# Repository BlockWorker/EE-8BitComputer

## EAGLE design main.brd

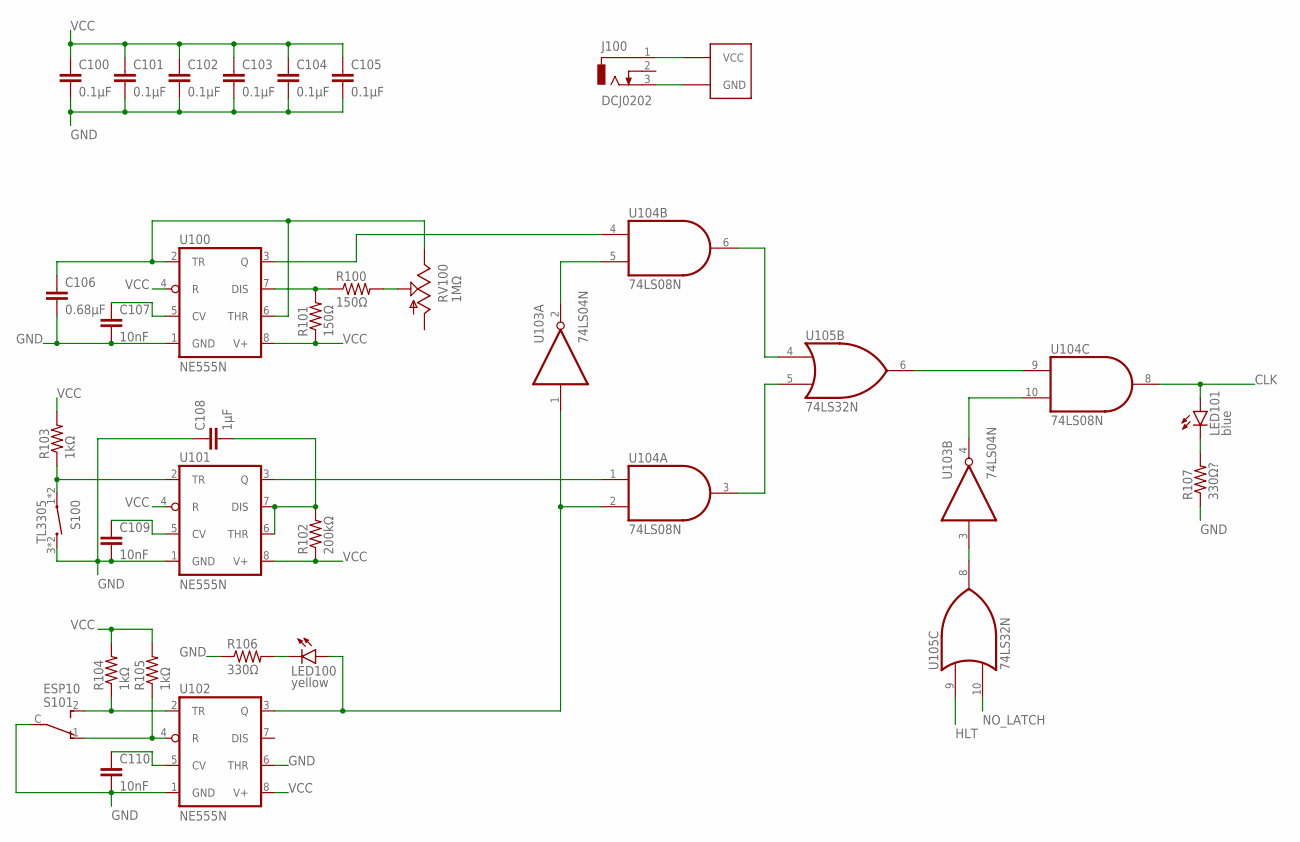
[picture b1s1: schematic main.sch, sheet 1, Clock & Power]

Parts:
C100, C101, C102, C103, C104, C105: 0.1µF; C0805K
C106: 0.68µF; C0805K
C107, C109, C110: 10nF; C0805K
C108: 1µF; C0805K
J100: DCJ0202
LED100: yellow; LED3MM
LED101: blue; LED3MM
R100, R101: 150Ω; R0805
R102: 200kΩ; R0805
R103, R104, R105: 1kΩ; R0805
R106: 330Ω; R0805
R107: 330Ω?; R0805
RV100: 1MΩ; CA9V
S100: TL3305; TL3305_MICROSWITCH
S101: ESP10
U100, U101, U102: NE555N; DIL08
U103: 74LS04N; DIL14
U104: 74LS08N; DIL14
U105: 74LS32N; DIL14

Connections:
!CLK_ENABLE: U103.3 (I), U105.8 (O)
!CLK_SWITCH: U103.2 (O), U104.5 (I1)
CLK: LED101.A, U104.8 (O); also elsewhere on the board
CLK_AUTO: U104.6 (O), U105.4 (I0)
CLK_AUTO_RAW: U100.3 (Q), U104.4 (I0)
CLK_ENABLE: U103.4 (O), U104.10 (I1)
CLK_MANUAL: U104.3 (O), U105.5 (I1)
CLK_MANUAL_RAW: U101.3 (Q), U104.1 (I0)
CLK_RAW: U104.9 (I0), U105.6 (O)
CLK_SWITCH: LED100.A, U102.3 (Q), U103.1 (I), U104.2 (I1)
GND: C100.2, C101.2, C102.2, C103.2, C104.2, C105.2, C106.2, C107.2, C108.1, C109.2, C110.2, J100.3, R106.1, R107.1, S100.3 (2), S100.4 (2), S101.C, U100.1 (GND), U101.1 (GND), U102.1 (GND), U102.6 (THR), U103.7 (GND), U104.7 (GND), U105.7 (GND); also elsewhere on the board
HLT: U105.9 (I0); also elsewhere on the board
LED100_GND: LED100.K (C), R106.2
LED101_GND: LED101.K (C), R107.2
NO_LATCH: U105.10 (I1); also elsewhere on the board
U100_CAP: C106.1, RV100.E, U100.2 (TR), U100.6 (THR)
U100_CV: C107.1, U100.5 (CV)
U100_DIS: R100.1, R101.2, U100.7 (DIS)
U100_DIS_INT: R100.2, RV100.S
U101_CAP: C108.2, R102.2, U101.6 (THR), U101.7 (DIS)
U101_CV: C109.1, U101.5 (CV)
U101_TR: R103.1, S100.1, S100.2 (1), U101.2 (TR)
U102_CV: C110.1, U102.5 (CV)
U102_R: R105.1, S101.1 (O), U102.4 (R)
U102_TR: R104.1, S101.2 (S), U102.2 (TR)
VCC: C100.1, C101.1, C102.1, C103.1, C104.1, C105.1, J100.1, R101.1, R102.1, R103.2, R104.2, R105.2, U100.4 (R), U100.8 (V+), U101.4 (R), U101.8 (V+), U102.8 (V+), U103.14 (VCC), U104.14 (VCC), U105.14 (VCC); also elsewhere on the board

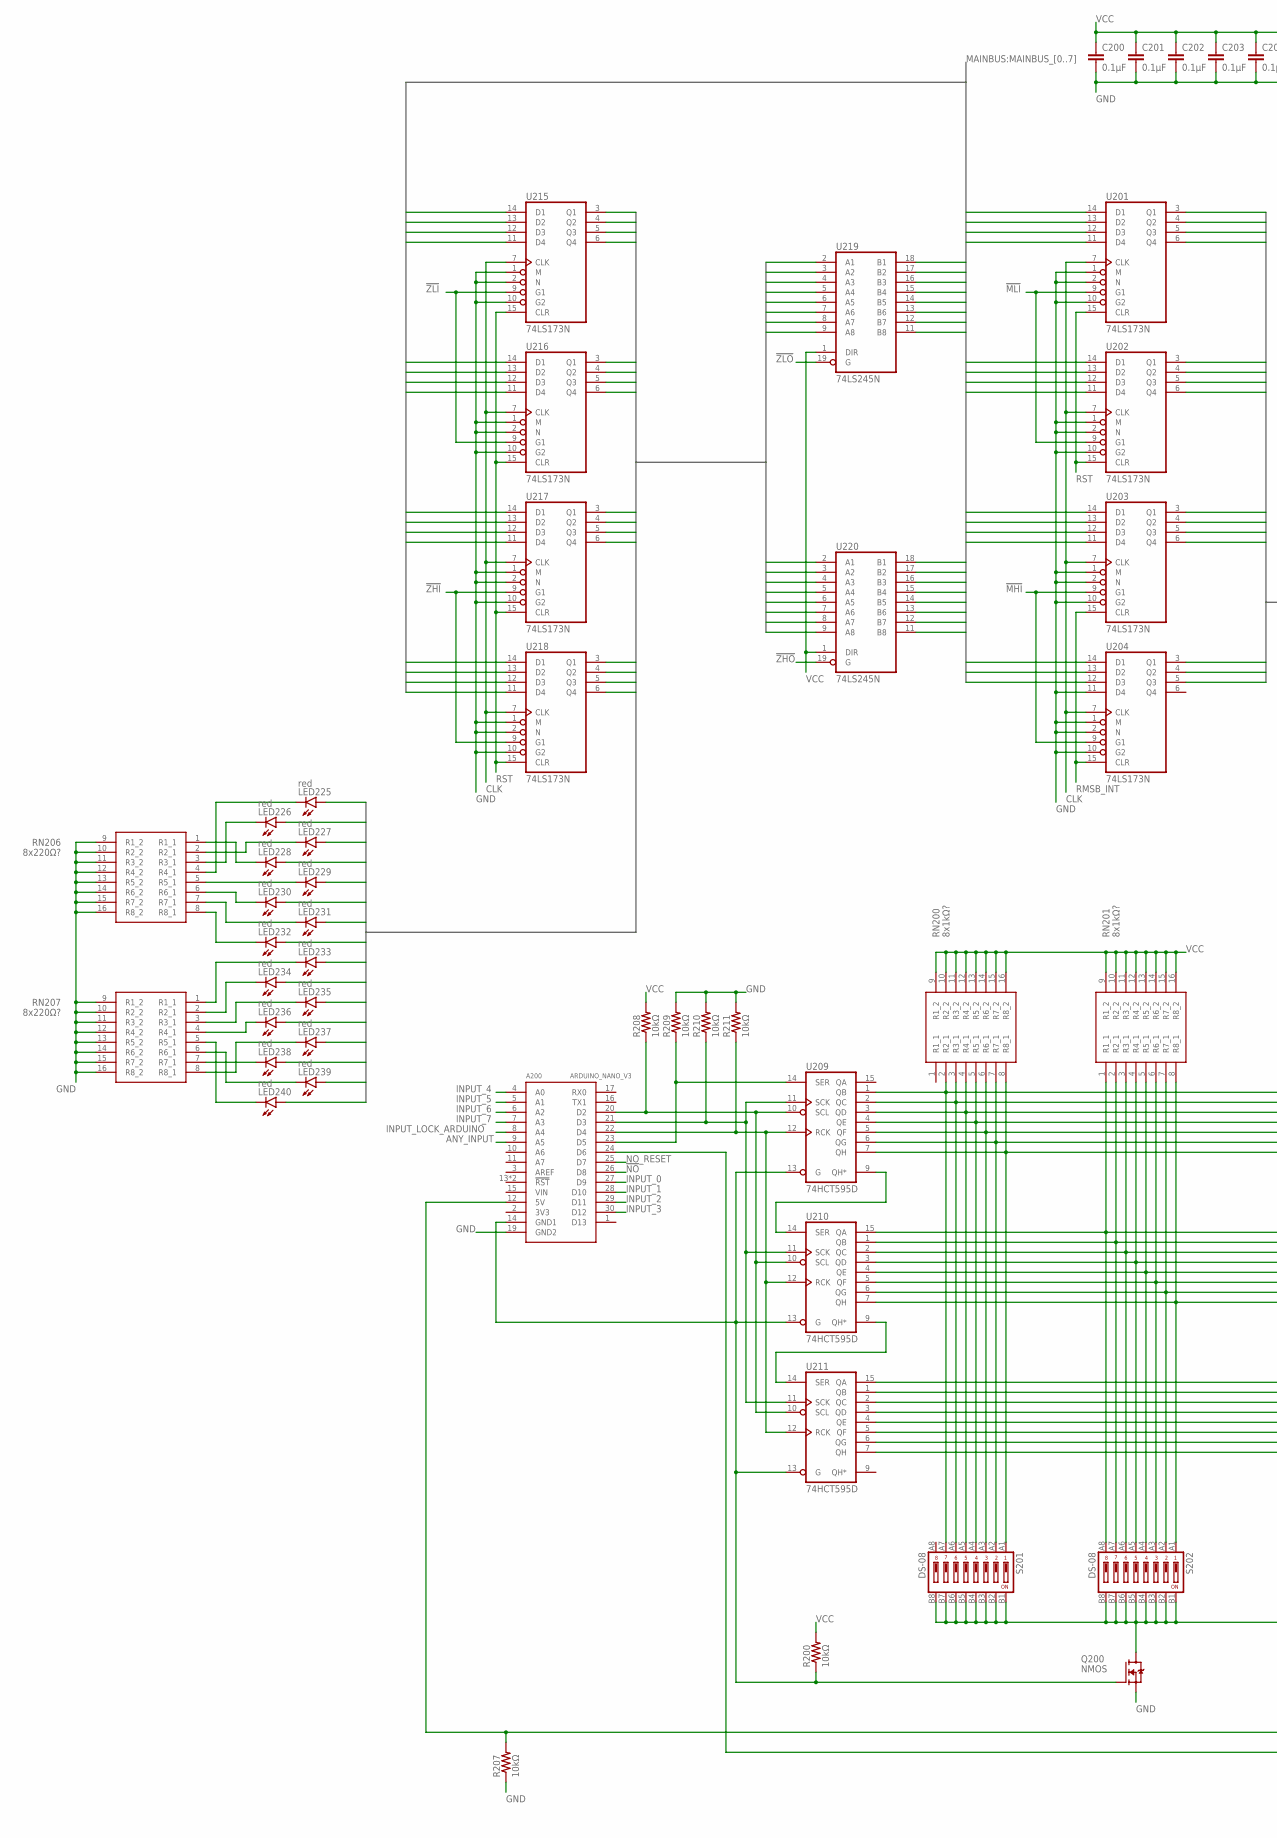
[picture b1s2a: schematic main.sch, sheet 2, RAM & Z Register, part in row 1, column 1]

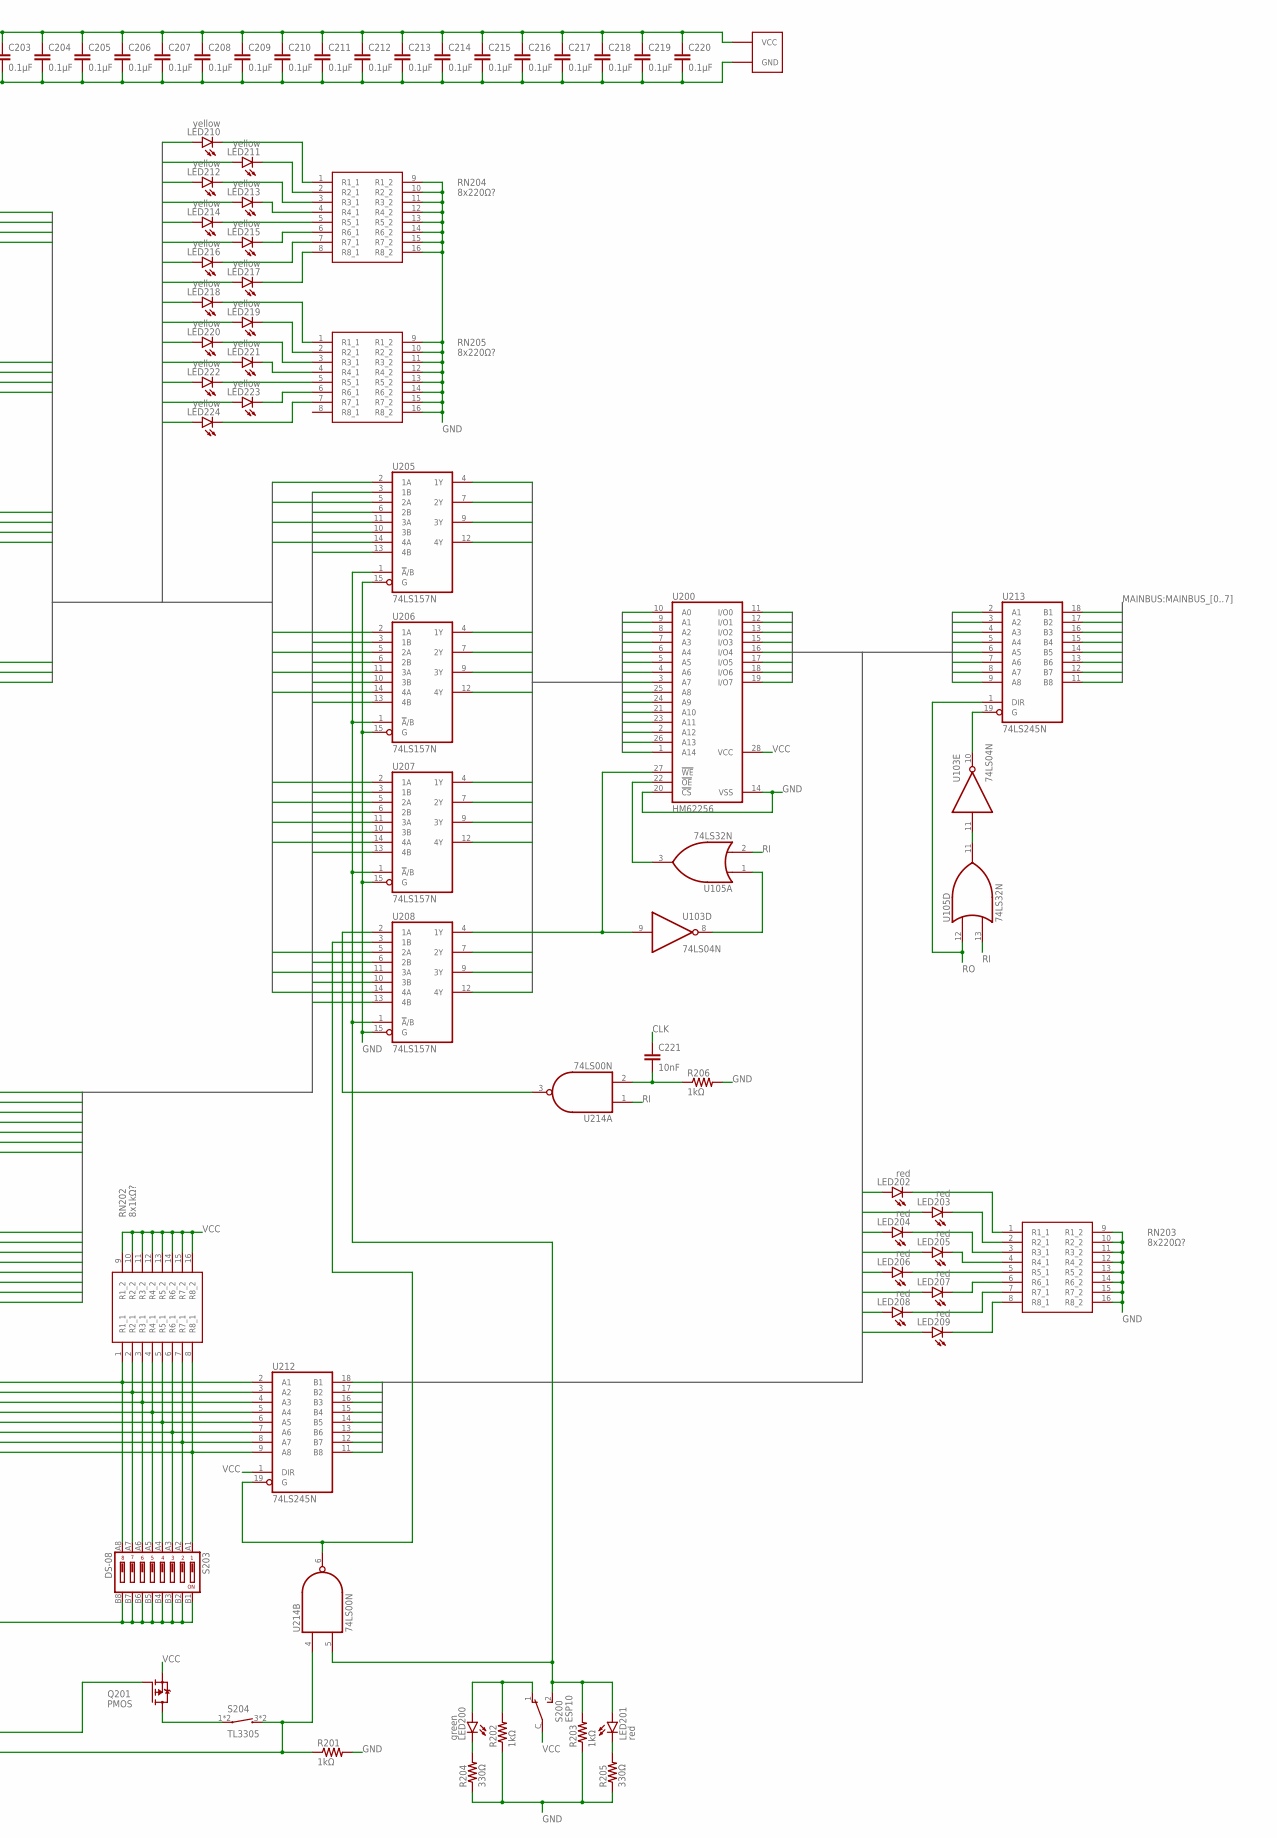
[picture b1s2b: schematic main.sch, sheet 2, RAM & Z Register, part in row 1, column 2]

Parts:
A200: ARDUINO_NANO_V3
C200, C201, C202, C203, C204, C205, C206, C207, C208, C209, C210, C211, C212, C213, C214, C215, C216, C217, C218, C219, C220: 0.1µF; C0805K
C221: 10nF; C0805K
LED200: green; LED3MM
LED201, LED202, LED203, LED204, LED205, LED206, LED207, LED208, LED209, LED225, LED226, LED227, LED228, LED229, LED230, LED231, LED232, LED233, LED234, LED235, LED236, LED237, LED238, LED239, LED240: red; LED3MM
LED210, LED211, LED212, LED213, LED214, LED215, LED216, LED217, LED218, LED219, LED220, LED221, LED222, LED223, LED224: yellow; LED3MM
Q200: NMOS; SOT23
Q201: PMOS; SOT23
R200, R207, R208, R209, R210, R211: 10kΩ; R0805
R201, R202, R203, R206: 1kΩ; R0805
R204, R205: 330Ω; R0805
RN200, RN201, RN202: 8x1kΩ?; CAY16102J8LF
RN203, RN204, RN205, RN206, RN207: 8x220Ω?; CAY16102J8LF
S200: ESP10
S201, S202, S203: DS-08; DIPSW-08
S204: TL3305; TL3305_MICROSWITCH
U103: 74LS04N; DIL14
U105: 74LS32N; DIL14
U200: HM62256; DIL28-6
U201, U202, U203, U204, U215, U216, U217, U218: 74LS173N; DIL16
U205, U206, U207, U208: 74LS157N; DIL16
U209, U210, U211: 74HCT595D; SO16
U212, U213, U219, U220: 74LS245N; DIL20
U214: 74LS00N; DIL14

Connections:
!MEM_IO_EN: U103.10 (O), U213.19 (G)
!MEM_MANMODE: LED200.A, R202.2, S200.1 (O)
!MHI: U203.9 (G1), U204.9 (G1); also elsewhere on the board
!MLI: U201.9 (G1), U202.9 (G1); also elsewhere on the board
!NO: A200.26 (D8); also elsewhere on the board
!ZHI: U217.9 (G1), U218.9 (G1); also elsewhere on the board
!ZHO: U220.19 (G); also elsewhere on the board
!ZLI: U215.9 (G1), U216.9 (G1); also elsewhere on the board
!ZLO: U219.19 (G); also elsewhere on the board
ANY_INPUT: A200.9 (A5); also elsewhere on the board
ARDUINO_5V_SENSE: A200.12 (5V), Q201.1 (G), R207.2
ARDUINO_DETECT_GND: A200.14 (GND1), Q200.1 (G), R200.1, U209.13 (G), U210.13 (G), U211.13 (G)
ARDUINO_SR_CHAIN1: U209.9 (QH*), U210.14 (SER)
ARDUINO_SR_CHAIN2: U210.9 (QH*), U211.14 (SER)
ARDUINO_SR_CLK: A200.21 (D3), R210.1, U209.11 (SCK), U210.11 (SCK), U211.11 (SCK)
ARDUINO_SR_CLR: A200.20 (D2), R208.1, U209.10 (SCL), U210.10 (SCL), U211.10 (SCL)
ARDUINO_SR_DATA: A200.23 (D5), R209.1, U209.14 (SER)
ARDUINO_SR_PUSH: A200.22 (D4), R211.1, U209.12 (RCK), U210.12 (RCK), U211.12 (RCK)
CLK: C221.1, U201.7 (CLK), U202.7 (CLK), U203.7 (CLK), U204.7 (CLK), U215.7 (CLK), U216.7 (CLK), U217.7 (CLK), U218.7 (CLK); also elsewhere on the board
GND: A200.19 (GND2), C200.2, C201.2, C202.2, C203.2, C204.2, C205.2, C206.2, C207.2, C208.2, C209.2, C210.2, C211.2, C212.2, C213.2, C214.2, C215.2, C216.2, C217.2, C218.2, C219.2, C220.2, Q200.2 (S), R201.2, R202.1, R203.1, R204.1, R205.1, R206.2, R207.1, R209.2, R210.2, R211.2, RN203.9 (R1_2), RN203.10 (R2_2), RN203.11 (R3_2), RN203.12 (R4_2), RN203.13 (R5_2), RN203.14 (R6_2), RN203.15 (R7_2), RN203.16 (R8_2), RN204.9 (R1_2), RN204.10 (R2_2), RN204.11 (R3_2), RN204.12 (R4_2), RN204.13 (R5_2), RN204.14 (R6_2), RN204.15 (R7_2), RN204.16 (R8_2), RN205.9 (R1_2), RN205.10 (R2_2), RN205.11 (R3_2), RN205.12 (R4_2), RN205.13 (R5_2), RN205.14 (R6_2), RN205.15 (R7_2), RN205.16 (R8_2), RN206.9 (R1_2), RN206.10 (R2_2), RN206.11 (R3_2), RN206.12 (R4_2), RN206.13 (R5_2), RN206.14 (R6_2), RN206.15 (R7_2), RN206.16 (R8_2), RN207.9 (R1_2), RN207.10 (R2_2), RN207.11 (R3_2), RN207.12 (R4_2), RN207.13 (R5_2), RN207.14 (R6_2), RN207.15 (R7_2), RN207.16 (R8_2), U103.7 (GND), U105.7 (GND), U200.14 (VSS), U200.20 (!CS), U201.1 (M), U201.2 (N), U201.8 (GND), U201.10 (G2), U202.1 (M), U202.2 (N), U202.8 (GND), U202.10 (G2), U203.1 (M), U203.2 (N), U203.8 (GND), U203.10 (G2), U204.1 (M), U204.2 (N), U204.8 (GND), U204.10 (G2), U204.11 (D4), U205.8 (GND), U205.15 (G), U206.8 (GND), U206.15 (G), U207.8 (GND), U207.15 (G), U208.8 (GND), U208.15 (G), U209.8 (GND), U210.8 (GND), U211.8 (GND), U212.10 (GND), U213.10 (GND), U214.7 (GND), U215.1 (M), U215.2 (N), U215.8 (GND), U215.10 (G2), U216.1 (M), U216.2 (N), U216.8 (GND), U216.10 (G2), U217.1 (M), U217.2 (N), U217.8 (GND), U217.10 (G2), U218.1 (M), U218.2 (N), U218.8 (GND), U218.10 (G2), U219.10 (GND), U220.10 (GND); also elsewhere on the board
INPUT_0: A200.27 (D9); also elsewhere on the board
INPUT_1: A200.28 (D10); also elsewhere on the board
INPUT_2: A200.29 (D11); also elsewhere on the board
INPUT_3: A200.30 (D12); also elsewhere on the board
INPUT_4: A200.4 (A0); also elsewhere on the board
INPUT_5: A200.5 (A1); also elsewhere on the board
INPUT_6: A200.6 (A2); also elsewhere on the board
INPUT_7: A200.7 (A3); also elsewhere on the board
INPUT_LOCK_ARDUINO: A200.8 (A4); also elsewhere on the board
LED202_GND: LED202.K (C), RN203.1 (R1_1)
LED203_GND: LED203.K (C), RN203.2 (R2_1)
LED204_GND: LED204.K (C), RN203.3 (R3_1)
LED205_GND: LED205.K (C), RN203.4 (R4_1)
LED206_GND: LED206.K (C), RN203.5 (R5_1)
LED207_GND: LED207.K (C), RN203.6 (R6_1)
LED208_GND: LED208.K (C), RN203.7 (R7_1)
LED209_GND: LED209.K (C), RN203.8 (R8_1)
LED210_GND: LED210.K (C), RN204.1 (R1_1)
LED211_GND: LED211.K (C), RN204.2 (R2_1)
LED212_GND: LED212.K (C), RN204.3 (R3_1)
LED213_GND: LED213.K (C), RN204.4 (R4_1)
LED214_GND: LED214.K (C), RN204.5 (R5_1)
LED215_GND: LED215.K (C), RN204.6 (R6_1)
LED216_GND: LED216.K (C), RN204.7 (R7_1)
LED217_GND: LED217.K (C), RN204.8 (R8_1)
LED218_GND: LED218.K (C), RN205.1 (R1_1)
LED219_GND: LED219.K (C), RN205.2 (R2_1)
LED220_GND: LED220.K (C), RN205.3 (R3_1)
LED221_GND: LED221.K (C), RN205.4 (R4_1)
LED222_GND: LED222.K (C), RN205.5 (R5_1)
LED223_GND: LED223.K (C), RN205.6 (R6_1)
LED224_GND: LED224.K (C), RN205.7 (R7_1)
LED225_GND: LED225.K (C), RN206.4 (R4_1)
LED226_GND: LED226.K (C), RN206.3 (R3_1)
LED227_GND: LED227.K (C), RN206.2 (R2_1)
LED228_GND: LED228.K (C), RN206.1 (R1_1)
LED229_GND: LED229.K (C), RN206.5 (R5_1)
LED230_GND: LED230.K (C), RN206.6 (R6_1)
LED231_GND: LED231.K (C), RN206.7 (R7_1)
LED232_GND: LED232.K (C), RN206.8 (R8_1)
LED233_GND: LED233.K (C), RN207.1 (R1_1)
LED234_GND: LED234.K (C), RN207.2 (R2_1)
LED235_GND: LED235.K (C), RN207.3 (R3_1)
LED236_GND: LED236.K (C), RN207.4 (R4_1)
LED237_GND: LED237.K (C), RN207.8 (R8_1)
LED238_GND: LED238.K (C), RN207.7 (R7_1)
LED239_GND: LED239.K (C), RN207.6 (R6_1)
LED240_GND: LED240.K (C), RN207.5 (R5_1)
MAINBUS_0: U201.14 (D1), U203.14 (D1), U213.18 (B1), U215.14 (D1), U217.14 (D1), U219.18 (B1), U220.18 (B1); also elsewhere on the board
MAINBUS_1: U201.13 (D2), U203.13 (D2), U213.17 (B2), U215.13 (D2), U217.13 (D2), U219.17 (B2), U220.17 (B2); also elsewhere on the board
MAINBUS_2: U201.12 (D3), U203.12 (D3), U213.16 (B3), U215.12 (D3), U217.12 (D3), U219.16 (B3), U220.16 (B3); also elsewhere on the board
MAINBUS_3: U201.11 (D4), U203.11 (D4), U213.15 (B4), U215.11 (D4), U217.11 (D4), U219.15 (B4), U220.15 (B4); also elsewhere on the board
MAINBUS_4: U202.14 (D1), U204.14 (D1), U213.14 (B5), U216.14 (D1), U218.14 (D1), U219.14 (B5), U220.14 (B5); also elsewhere on the board
MAINBUS_5: U202.13 (D2), U204.13 (D2), U213.13 (B6), U216.13 (D2), U218.13 (D2), U219.13 (B6), U220.13 (B6); also elsewhere on the board
MAINBUS_6: U202.12 (D3), U204.12 (D3), U213.12 (B7), U216.12 (D3), U218.12 (D3), U219.12 (B7), U220.12 (B7); also elsewhere on the board
MAINBUS_7: U202.11 (D4), U213.11 (B8), U216.11 (D4), U218.11 (D4), U219.11 (B8), U220.11 (B8); also elsewhere on the board
MEMADDR_0: U200.10 (A0), U205.4 (1Y)
MEMADDR_1: U200.9 (A1), U205.7 (2Y)
MEMADDR_2: U200.8 (A2), U205.12 (4Y)
MEMADDR_3: U200.7 (A3), U205.9 (3Y)
MEMADDR_4: U200.6 (A4), U206.7 (2Y)
MEMADDR_5: U200.5 (A5), U206.4 (1Y)
MEMADDR_6: U200.4 (A6), U206.9 (3Y)
MEMADDR_7: U200.3 (A7), U206.12 (4Y)
MEMADDR_8: U200.25 (A8), U207.7 (2Y)
MEMADDR_9: U200.24 (A9), U207.4 (1Y)
MEMADDR_10: U200.21 (A10), U207.12 (4Y)
MEMADDR_11: U200.23 (A11), U207.9 (3Y)
MEMADDR_12: U200.2 (A12), U208.12 (4Y)
MEMADDR_13: U200.26 (A13), U208.7 (2Y)
MEMADDR_14: U200.1 (A14), U208.9 (3Y)
MEMADDR_AUTO_0: LED210.A, U201.3 (Q1), U205.2 (1A)
MEMADDR_AUTO_1: LED211.A, U201.4 (Q2), U205.5 (2A)
MEMADDR_AUTO_2: LED212.A, U201.5 (Q3), U205.14 (4A)
MEMADDR_AUTO_3: LED213.A, U201.6 (Q4), U205.11 (3A)
MEMADDR_AUTO_4: LED214.A, U202.3 (Q1), U206.5 (2A)
MEMADDR_AUTO_5: LED215.A, U202.4 (Q2), U206.2 (1A)
MEMADDR_AUTO_6: LED216.A, U202.5 (Q3), U206.11 (3A)
MEMADDR_AUTO_7: LED217.A, U202.6 (Q4), U206.14 (4A)
MEMADDR_AUTO_8: LED218.A, U203.3 (Q1), U207.5 (2A)
MEMADDR_AUTO_9: LED219.A, U203.4 (Q2), U207.2 (1A)
MEMADDR_AUTO_10: LED220.A, U203.5 (Q3), U207.14 (4A)
MEMADDR_AUTO_11: LED221.A, U203.6 (Q4), U207.11 (3A)
MEMADDR_AUTO_12: LED222.A, U204.3 (Q1), U208.14 (4A)
MEMADDR_AUTO_13: LED223.A, U204.4 (Q2), U208.5 (2A)
MEMADDR_AUTO_14: LED224.A, U204.5 (Q3), U208.11 (3A)
MEMADDR_MAN_0: RN201.8 (R8_1), S202.A1 (1), U205.3 (1B), U210.7 (QH)
MEMADDR_MAN_1: RN201.7 (R7_1), S202.A2 (2), U205.6 (2B), U210.6 (QG)
MEMADDR_MAN_2: RN201.6 (R6_1), S202.A3 (3), U205.13 (4B), U210.5 (QF)
MEMADDR_MAN_3: RN201.5 (R5_1), S202.A4 (4), U205.10 (3B), U210.4 (QE)
MEMADDR_MAN_4: RN201.4 (R4_1), S202.A5 (5), U206.6 (2B), U210.3 (QD)
MEMADDR_MAN_5: RN201.3 (R3_1), S202.A6 (6), U206.3 (1B), U210.2 (QC)
MEMADDR_MAN_6: RN201.2 (R2_1), S202.A7 (7), U206.10 (3B), U210.1 (QB)
MEMADDR_MAN_7: RN201.1 (R1_1), S202.A8 (8), U206.13 (4B), U210.15 (QA)
MEMADDR_MAN_8: RN200.8 (R8_1), S201.A1 (1), U207.6 (2B), U209.7 (QH)
MEMADDR_MAN_9: RN200.7 (R7_1), S201.A2 (2), U207.3 (1B), U209.6 (QG)
MEMADDR_MAN_10: RN200.6 (R6_1), S201.A3 (3), U207.13 (4B), U209.5 (QF)
MEMADDR_MAN_11: RN200.5 (R5_1), S201.A4 (4), U207.10 (3B), U209.4 (QE)
MEMADDR_MAN_12: RN200.4 (R4_1), S201.A5 (5), U208.13 (4B), U209.3 (QD)
MEMADDR_MAN_13: RN200.3 (R3_1), S201.A6 (6), U208.6 (2B), U209.2 (QC)
MEMADDR_MAN_14: RN200.2 (R2_1), S201.A7 (7), U208.10 (3B), U209.1 (QB)
MEMIO_0: LED202.A, U200.11 (I/O0), U212.11 (B8), U213.2 (A1)
MEMIO_1: LED203.A, U200.12 (I/O1), U212.12 (B7), U213.3 (A2)
MEMIO_2: LED204.A, U200.13 (I/O2), U212.13 (B6), U213.4 (A3)
MEMIO_3: LED205.A, U200.15 (I/O3), U212.14 (B5), U213.5 (A4)
MEMIO_4: LED206.A, U200.16 (I/O4), U212.15 (B4), U213.6 (A5)
MEMIO_5: LED207.A, U200.17 (I/O5), U212.16 (B3), U213.7 (A6)
MEMIO_6: LED208.A, U200.18 (I/O6), U212.17 (B2), U213.8 (A7)
MEMIO_7: LED209.A, U200.19 (I/O7), U212.18 (B1), U213.9 (A8)
MEMIO_MAN_0: RN202.8 (R8_1), S203.A1 (1), U211.7 (QH), U212.9 (A8)
MEMIO_MAN_1: RN202.7 (R7_1), S203.A2 (2), U211.6 (QG), U212.8 (A7)
MEMIO_MAN_2: RN202.6 (R6_1), S203.A3 (3), U211.5 (QF), U212.7 (A6)
MEMIO_MAN_3: RN202.5 (R5_1), S203.A4 (4), U211.4 (QE), U212.6 (A5)
MEMIO_MAN_4: RN202.4 (R4_1), S203.A5 (5), U211.3 (QD), U212.5 (A4)
MEMIO_MAN_5: RN202.3 (R3_1), S203.A6 (6), U211.2 (QC), U212.4 (A3)
MEMIO_MAN_6: RN202.2 (R2_1), S203.A7 (7), U211.1 (QB), U212.3 (A2)
MEMIO_MAN_7: RN202.1 (R1_1), S203.A8 (8), U211.15 (QA), U212.2 (A1)
MEM_!MANMODE!_LED: LED200.K (C), R204.2
MEM_!OE: U105.3 (O), U200.22 (!OE)
MEM_!OE_INT: U103.8 (O), U105.1 (I0)
MEM_!WE: U103.9 (I), U200.27 (!WE), U208.4 (1Y)
MEM_!WE!_AUTO: U208.2 (1A), U214.3 (O)
MEM_!WE!_MAN: U208.3 (1B), U212.19 (G), U214.6 (O)
MEM_CLK_PULSE: C221.2, R206.1, U214.2 (I1)
MEM_IO_EN: U103.11 (I), U105.11 (O)
MEM_MANMODE: LED201.A, R203.2, S200.2 (S), U205.1 (!A!/B), U206.1 (!A!/B), U207.1 (!A!/B), U208.1 (!A!/B), U214.5 (I1)
MEM_MANMODE_LED: LED201.K (C), R205.2
MEM_MAN_GND: Q200.3 (D), S201.B1 (16), S201.B2 (15), S201.B3 (14), S201.B4 (13), S201.B5 (12), S201.B6 (11), S201.B7 (10), S201.B8 (9), S202.B1 (16), S202.B2 (15), S202.B3 (14), S202.B4 (13), S202.B5 (12), S202.B6 (11), S202.B7 (10), S202.B8 (9), S203.B1 (16), S203.B2 (15), S203.B3 (14), S203.B4 (13), S203.B5 (12), S203.B6 (11), S203.B7 (10), S203.B8 (9)
MEM_MAN_VCC: Q201.3 (D), S204.1, S204.2 (1)
MEM_MAN_WRITE: A200.24 (D6), R201.1, S204.3 (2), S204.4 (2), U214.4 (I0)
NO_RESET: A200.25 (D7); also elsewhere on the board
REG_Z_0: LED225.A, U215.3 (Q1), U219.2 (A1)
REG_Z_1: LED226.A, U215.4 (Q2), U219.3 (A2)
REG_Z_2: LED227.A, U215.5 (Q3), U219.4 (A3)
REG_Z_3: LED228.A, U215.6 (Q4), U219.5 (A4)
REG_Z_4: LED229.A, U216.3 (Q1), U219.6 (A5)
REG_Z_5: LED230.A, U216.4 (Q2), U219.7 (A6)
REG_Z_6: LED231.A, U216.5 (Q3), U219.8 (A7)
REG_Z_7: LED232.A, U216.6 (Q4), U219.9 (A8)
REG_Z_8: LED233.A, U217.3 (Q1), U220.2 (A1)
REG_Z_9: LED234.A, U217.4 (Q2), U220.3 (A2)
REG_Z_10: LED235.A, U217.5 (Q3), U220.4 (A3)
REG_Z_11: LED236.A, U217.6 (Q4), U220.5 (A4)
REG_Z_12: LED237.A, U218.3 (Q1), U220.6 (A5)
REG_Z_13: LED238.A, U218.4 (Q2), U220.7 (A6)
REG_Z_14: LED239.A, U218.5 (Q3), U220.8 (A7)
REG_Z_15: LED240.A, U218.6 (Q4), U220.9 (A8)
RI: U105.2 (I1), U105.13 (I1), U214.1 (I0); also elsewhere on the board
RMSB_INT: U203.15 (CLR), U204.15 (CLR); also elsewhere on the board
RO: U105.12 (I0), U213.1 (DIR); also elsewhere on the board
RST: U201.15 (CLR), U202.15 (CLR), U215.15 (CLR), U216.15 (CLR), U217.15 (CLR), U218.15 (CLR); also elsewhere on the board
VCC: C200.1, C201.1, C202.1, C203.1, C204.1, C205.1, C206.1, C207.1, C208.1, C209.1, C210.1, C211.1, C212.1, C213.1, C214.1, C215.1, C216.1, C217.1, C218.1, C219.1, C220.1, Q201.2 (S), R200.2, R208.2, RN200.9 (R1_2), RN200.10 (R2_2), RN200.11 (R3_2), RN200.12 (R4_2), RN200.13 (R5_2), RN200.14 (R6_2), RN200.15 (R7_2), RN200.16 (R8_2), RN201.9 (R1_2), RN201.10 (R2_2), RN201.11 (R3_2), RN201.12 (R4_2), RN201.13 (R5_2), RN201.14 (R6_2), RN201.15 (R7_2), RN201.16 (R8_2), RN202.9 (R1_2), RN202.10 (R2_2), RN202.11 (R3_2), RN202.12 (R4_2), RN202.13 (R5_2), RN202.14 (R6_2), RN202.15 (R7_2), RN202.16 (R8_2), S200.C, U103.14 (VCC), U105.14 (VCC), U200.28 (VCC), U201.16 (VCC), U202.16 (VCC), U203.16 (VCC), U204.16 (VCC), U205.16 (VCC), U206.16 (VCC), U207.16 (VCC), U208.16 (VCC), U209.16 (VCC), U210.16 (VCC), U211.16 (VCC), U212.1 (DIR), U212.20 (VCC), U213.20 (VCC), U214.14 (VCC), U215.16 (VCC), U216.16 (VCC), U217.16 (VCC), U218.16 (VCC), U219.1 (DIR), U219.20 (VCC), U220.1 (DIR), U220.20 (VCC); also elsewhere on the board

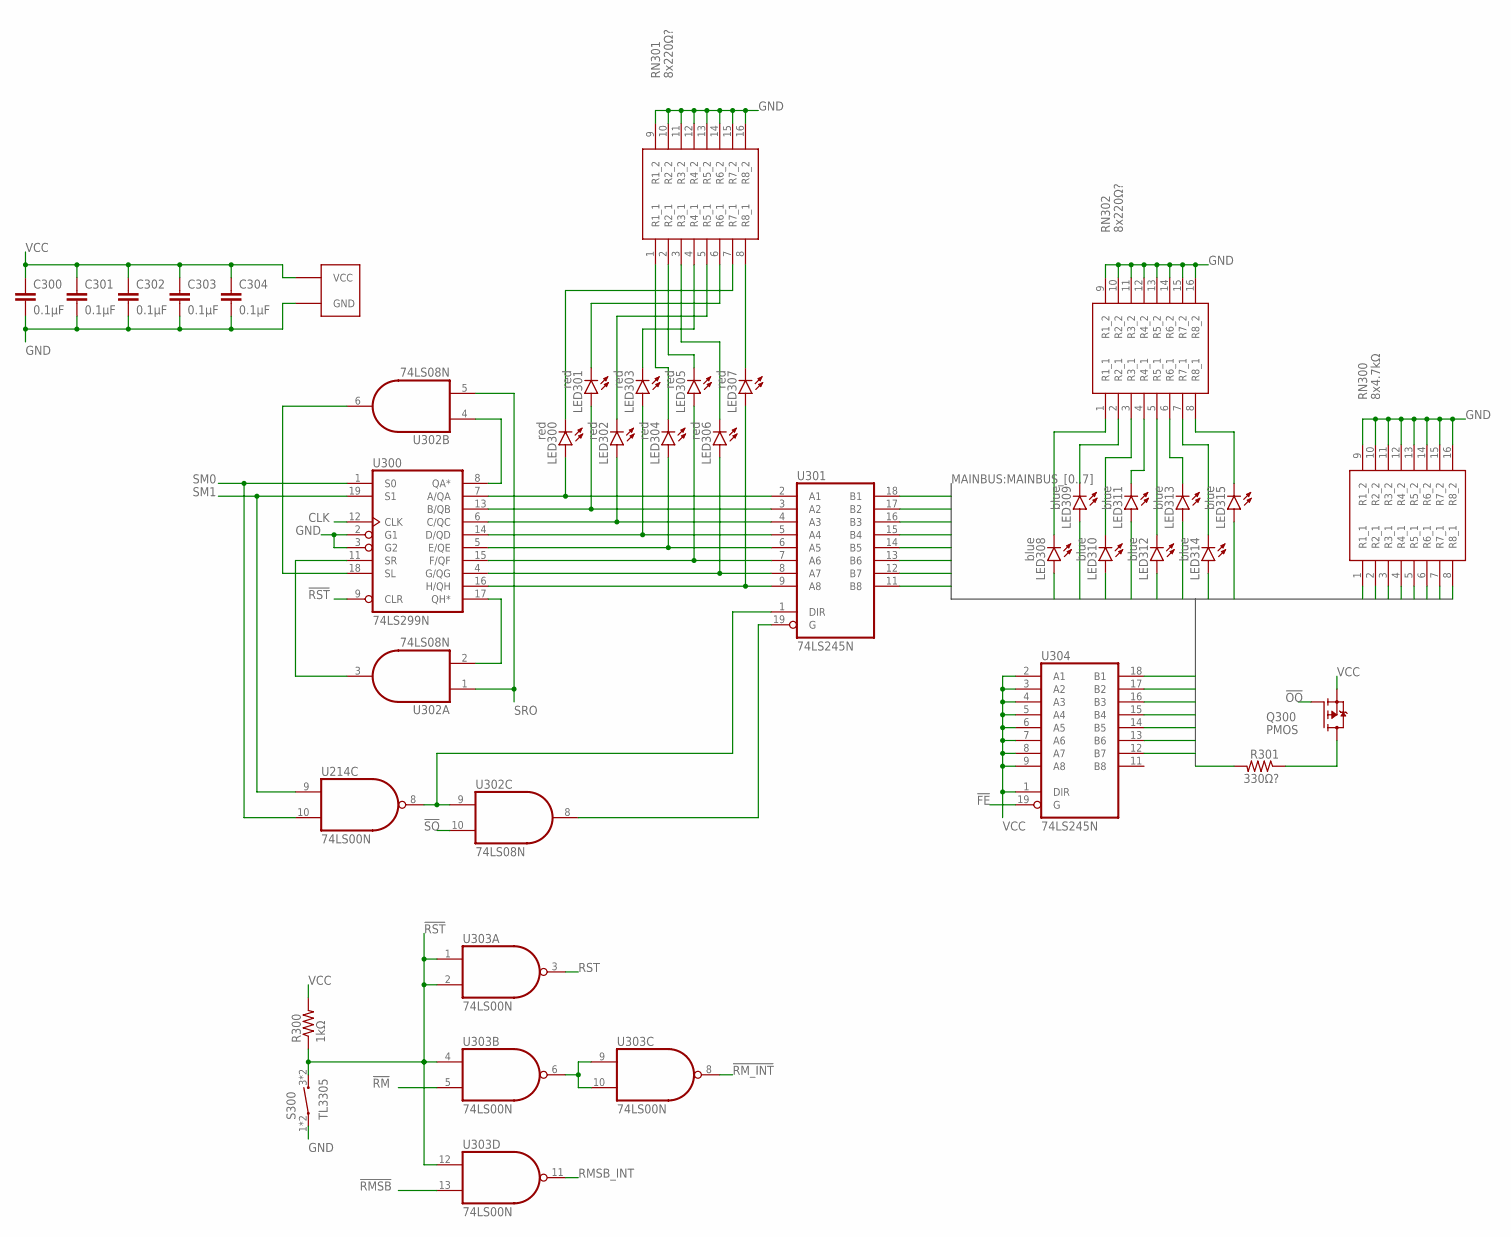
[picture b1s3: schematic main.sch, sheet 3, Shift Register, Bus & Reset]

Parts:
C300, C301, C302, C303, C304: 0.1µF; C0805K
LED300, LED301, LED302, LED303, LED304, LED305, LED306, LED307: red; LED3MM
LED308, LED309, LED310, LED311, LED312, LED313, LED314, LED315: blue; LED3MM
Q300: PMOS; SOT23
R300: 1kΩ; R0805
R301: 330Ω?; R0805
RN300: 8x4.7kΩ; CAY16102J8LF
RN301, RN302: 8x220Ω?; CAY16102J8LF
S300: TL3305; TL3305_MICROSWITCH
U214, U303: 74LS00N; DIL14
U300: 74LS299N; DIL20
U301, U304: 74LS245N; DIL20
U302: 74LS08N; DIL14

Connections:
!FE: U304.19 (G); also elsewhere on the board
!OO: Q300.1 (G); also elsewhere on the board
!RM: U303.5 (I1); also elsewhere on the board
!RMSB: U303.13 (I1); also elsewhere on the board
!RM_INT: U303.8 (O); also elsewhere on the board
!RST: R300.1, S300.3 (2), S300.4 (2), U300.9 (CLR), U303.1 (I0), U303.2 (I1), U303.4 (I0), U303.12 (I0); also elsewhere on the board
!SHIFT_IO_EN: U301.19 (G), U302.8 (O)
!SO: U302.10 (I1); also elsewhere on the board
BUS_OO: Q300.3 (D), R301.1
CLK: U300.12 (CLK); also elsewhere on the board
GND: C300.2, C301.2, C302.2, C303.2, C304.2, RN300.9 (R1_2), RN300.10 (R2_2), RN300.11 (R3_2), RN300.12 (R4_2), RN300.13 (R5_2), RN300.14 (R6_2), RN300.15 (R7_2), RN300.16 (R8_2), RN301.9 (R1_2), RN301.10 (R2_2), RN301.11 (R3_2), RN301.12 (R4_2), RN301.13 (R5_2), RN301.14 (R6_2), RN301.15 (R7_2), RN301.16 (R8_2), RN302.9 (R1_2), RN302.10 (R2_2), RN302.11 (R3_2), RN302.12 (R4_2), RN302.13 (R5_2), RN302.14 (R6_2), RN302.15 (R7_2), RN302.16 (R8_2), S300.1, S300.2 (1), U214.7 (GND), U300.2 (G1), U300.3 (G2), U300.10 (GND), U301.10 (GND), U302.7 (GND), U303.7 (GND), U304.10 (GND); also elsewhere on the board
LED300_GND: LED300.K (C), RN301.7 (R7_1)
LED301_GND: LED301.K (C), RN301.6 (R6_1)
LED302_GND: LED302.K (C), RN301.5 (R5_1)
LED303_GND: LED303.K (C), RN301.4 (R4_1)
LED304_GND: LED304.K (C), RN301.1 (R1_1)
LED305_GND: LED305.K (C), RN301.2 (R2_1)
LED306_GND: LED306.K (C), RN301.3 (R3_1)
LED307_GND: LED307.K (C), RN301.8 (R8_1)
LED308_GND: LED308.K (C), RN302.1 (R1_1)
LED309_GND: LED309.K (C), RN302.2 (R2_1)
LED310_GND: LED310.K (C), RN302.3 (R3_1)
LED311_GND: LED311.K (C), RN302.4 (R4_1)
LED312_GND: LED312.K (C), RN302.5 (R5_1)
LED313_GND: LED313.K (C), RN302.6 (R6_1)
LED314_GND: LED314.K (C), RN302.7 (R7_1)
LED315_GND: LED315.K (C), RN302.8 (R8_1)
MAINBUS_0: LED315.A, R301.2, RN300.8 (R8_1), U301.11 (B8); also elsewhere on the board
MAINBUS_1: LED314.A, RN300.7 (R7_1), U301.12 (B7), U304.12 (B7); also elsewhere on the board
MAINBUS_2: LED313.A, RN300.6 (R6_1), U301.13 (B6), U304.13 (B6); also elsewhere on the board
MAINBUS_3: LED312.A, RN300.5 (R5_1), U301.14 (B5), U304.14 (B5); also elsewhere on the board
MAINBUS_4: LED311.A, RN300.4 (R4_1), U301.15 (B4), U304.15 (B4); also elsewhere on the board
MAINBUS_5: LED310.A, RN300.3 (R3_1), U301.16 (B3), U304.16 (B3); also elsewhere on the board
MAINBUS_6: LED309.A, RN300.2 (R2_1), U301.17 (B2), U304.17 (B2); also elsewhere on the board
MAINBUS_7: LED308.A, RN300.1 (R1_1), U301.18 (B1), U304.18 (B1); also elsewhere on the board
RMSB_INT: U303.11 (O); also elsewhere on the board
RM_INT: U303.6 (O), U303.9 (I0), U303.10 (I1)
RST: U303.3 (O); also elsewhere on the board
SHIFT_IO_0: LED307.A, U300.16 (H/QH), U301.9 (A8)
SHIFT_IO_1: LED306.A, U300.4 (G/QG), U301.8 (A7)
SHIFT_IO_2: LED305.A, U300.15 (F/QF), U301.7 (A6)
SHIFT_IO_3: LED304.A, U300.5 (E/QE), U301.6 (A5)
SHIFT_IO_4: LED303.A, U300.14 (D/QD), U301.5 (A4)
SHIFT_IO_5: LED302.A, U300.6 (C/QC), U301.4 (A3)
SHIFT_IO_6: LED301.A, U300.13 (B/QB), U301.3 (A2)
SHIFT_IO_7: LED300.A, U300.7 (A/QA), U301.2 (A1)
SHIFT_IO_DIR: U214.8 (O), U301.1 (DIR), U302.9 (I0)
SHIFT_LEFT_FEEDBACK: U300.18 (SL), U302.6 (O)
SHIFT_LEFT_FEEDBACK_RAW: U300.8 (QA*), U302.4 (I0)
SHIFT_RIGHT_FEEDBACK: U300.11 (SR), U302.3 (O)
SHIFT_RIGHT_FEEDBACK_RAW: U300.17 (QH*), U302.2 (I1)
SM0: U214.10 (I1), U300.1 (S0); also elsewhere on the board
SM1: U214.9 (I0), U300.19 (S1); also elsewhere on the board
SRO: U302.1 (I0), U302.5 (I1); also elsewhere on the board
VCC: C300.1, C301.1, C302.1, C303.1, C304.1, Q300.2 (S), R300.2, U214.14 (VCC), U300.20 (VCC), U301.20 (VCC), U302.14 (VCC), U303.14 (VCC), U304.1 (DIR), U304.2 (A1), U304.3 (A2), U304.4 (A3), U304.5 (A4), U304.6 (A5), U304.7 (A6), U304.8 (A7), U304.9 (A8), U304.20 (VCC); also elsewhere on the board

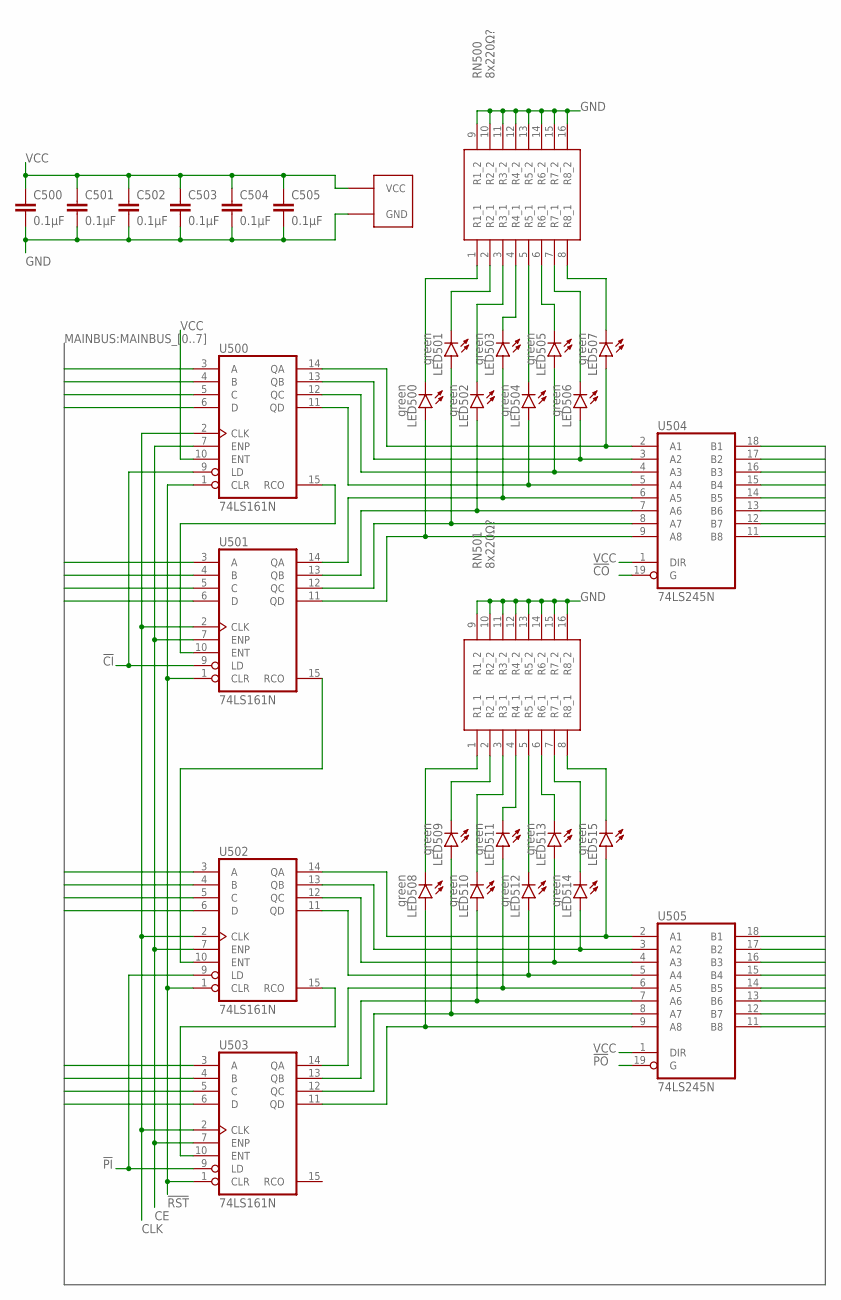
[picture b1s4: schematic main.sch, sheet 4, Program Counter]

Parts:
C500, C501, C502, C503, C504, C505: 0.1µF; C0805K
LED500, LED501, LED502, LED503, LED504, LED505, LED506, LED507, LED508, LED509, LED510, LED511, LED512, LED513, LED514, LED515: green; LED3MM
RN500, RN501: 8x220Ω?; CAY16102J8LF
U500, U501, U502, U503: 74LS161N; DIL16
U504, U505: 74LS245N; DIL20

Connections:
!CI: U500.9 (LD), U501.9 (LD); also elsewhere on the board
!CO: U504.19 (G); also elsewhere on the board
!PI: U502.9 (LD), U503.9 (LD); also elsewhere on the board
!PO: U505.19 (G); also elsewhere on the board
!RST: U500.1 (CLR), U501.1 (CLR), U502.1 (CLR), U503.1 (CLR); also elsewhere on the board
CE: U500.7 (ENP), U501.7 (ENP), U502.7 (ENP), U503.7 (ENP); also elsewhere on the board
CLK: U500.2 (CLK), U501.2 (CLK), U502.2 (CLK), U503.2 (CLK); also elsewhere on the board
COUNTER_0: LED507.A, U500.14 (QA), U504.2 (A1)
COUNTER_1: LED506.A, U500.13 (QB), U504.3 (A2)
COUNTER_2: LED505.A, U500.12 (QC), U504.4 (A3)
COUNTER_3: LED504.A, U500.11 (QD), U504.5 (A4)
COUNTER_4: LED503.A, U501.14 (QA), U504.6 (A5)
COUNTER_5: LED502.A, U501.13 (QB), U504.7 (A6)
COUNTER_6: LED501.A, U501.12 (QC), U504.8 (A7)
COUNTER_7: LED500.A, U501.11 (QD), U504.9 (A8)
COUNTER_RIPPLE_1: U500.15 (RCO), U501.10 (ENT)
COUNTER_RIPPLE_2: U501.15 (RCO), U502.10 (ENT)
COUNTER_RIPPLE_3: U502.15 (RCO), U503.10 (ENT)
GND: C500.2, C501.2, C502.2, C503.2, C504.2, C505.2, RN500.9 (R1_2), RN500.10 (R2_2), RN500.11 (R3_2), RN500.12 (R4_2), RN500.13 (R5_2), RN500.14 (R6_2), RN500.15 (R7_2), RN500.16 (R8_2), RN501.9 (R1_2), RN501.10 (R2_2), RN501.11 (R3_2), RN501.12 (R4_2), RN501.13 (R5_2), RN501.14 (R6_2), RN501.15 (R7_2), RN501.16 (R8_2), U500.8 (GND), U501.8 (GND), U502.8 (GND), U503.8 (GND), U504.10 (GND), U505.10 (GND); also elsewhere on the board
LED500_GND: LED500.K (C), RN500.1 (R1_1)
LED501_GND: LED501.K (C), RN500.2 (R2_1)
LED502_GND: LED502.K (C), RN500.3 (R3_1)
LED503_GND: LED503.K (C), RN500.4 (R4_1)
LED504_GND: LED504.K (C), RN500.5 (R5_1)
LED505_GND: LED505.K (C), RN500.6 (R6_1)
LED506_GND: LED506.K (C), RN500.7 (R7_1)
LED507_GND: LED507.K (C), RN500.8 (R8_1)
LED508_GND: LED508.K (C), RN501.1 (R1_1)
LED509_GND: LED509.K (C), RN501.2 (R2_1)
LED510_GND: LED510.K (C), RN501.3 (R3_1)
LED511_GND: LED511.K (C), RN501.4 (R4_1)
LED512_GND: LED512.K (C), RN501.5 (R5_1)
LED513_GND: LED513.K (C), RN501.6 (R6_1)
LED514_GND: LED514.K (C), RN501.7 (R7_1)
LED515_GND: LED515.K (C), RN501.8 (R8_1)
MAINBUS_0: U500.3 (A), U502.3 (A), U504.18 (B1), U505.18 (B1); also elsewhere on the board
MAINBUS_1: U500.4 (B), U502.4 (B), U504.17 (B2), U505.17 (B2); also elsewhere on the board
MAINBUS_2: U500.5 (C), U502.5 (C), U504.16 (B3), U505.16 (B3); also elsewhere on the board
MAINBUS_3: U500.6 (D), U502.6 (D), U504.15 (B4), U505.15 (B4); also elsewhere on the board
MAINBUS_4: U501.3 (A), U503.3 (A), U504.14 (B5), U505.14 (B5); also elsewhere on the board
MAINBUS_5: U501.4 (B), U503.4 (B), U504.13 (B6), U505.13 (B6); also elsewhere on the board
MAINBUS_6: U501.5 (C), U503.5 (C), U504.12 (B7), U505.12 (B7); also elsewhere on the board
MAINBUS_7: U501.6 (D), U503.6 (D), U504.11 (B8), U505.11 (B8); also elsewhere on the board
PAGE_0: LED515.A, U502.14 (QA), U505.2 (A1)
PAGE_1: LED514.A, U502.13 (QB), U505.3 (A2)
PAGE_2: LED513.A, U502.12 (QC), U505.4 (A3)
PAGE_3: LED512.A, U502.11 (QD), U505.5 (A4)
PAGE_4: LED511.A, U503.14 (QA), U505.6 (A5)
PAGE_5: LED510.A, U503.13 (QB), U505.7 (A6)
PAGE_6: LED509.A, U503.12 (QC), U505.8 (A7)
PAGE_7: LED508.A, U503.11 (QD), U505.9 (A8)
VCC: C500.1, C501.1, C502.1, C503.1, C504.1, C505.1, U500.10 (ENT), U500.16 (VCC), U501.16 (VCC), U502.16 (VCC), U503.16 (VCC), U504.1 (DIR), U504.20 (VCC), U505.1 (DIR), U505.20 (VCC); also elsewhere on the board

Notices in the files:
main.brd:
©2019 BlockWorker
